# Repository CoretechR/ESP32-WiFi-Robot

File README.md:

# ESP32-WiFi-Robot
ESP32 Powered Video Streaming Robot

Python is needed to convert the website file from HTML to a single string and back.

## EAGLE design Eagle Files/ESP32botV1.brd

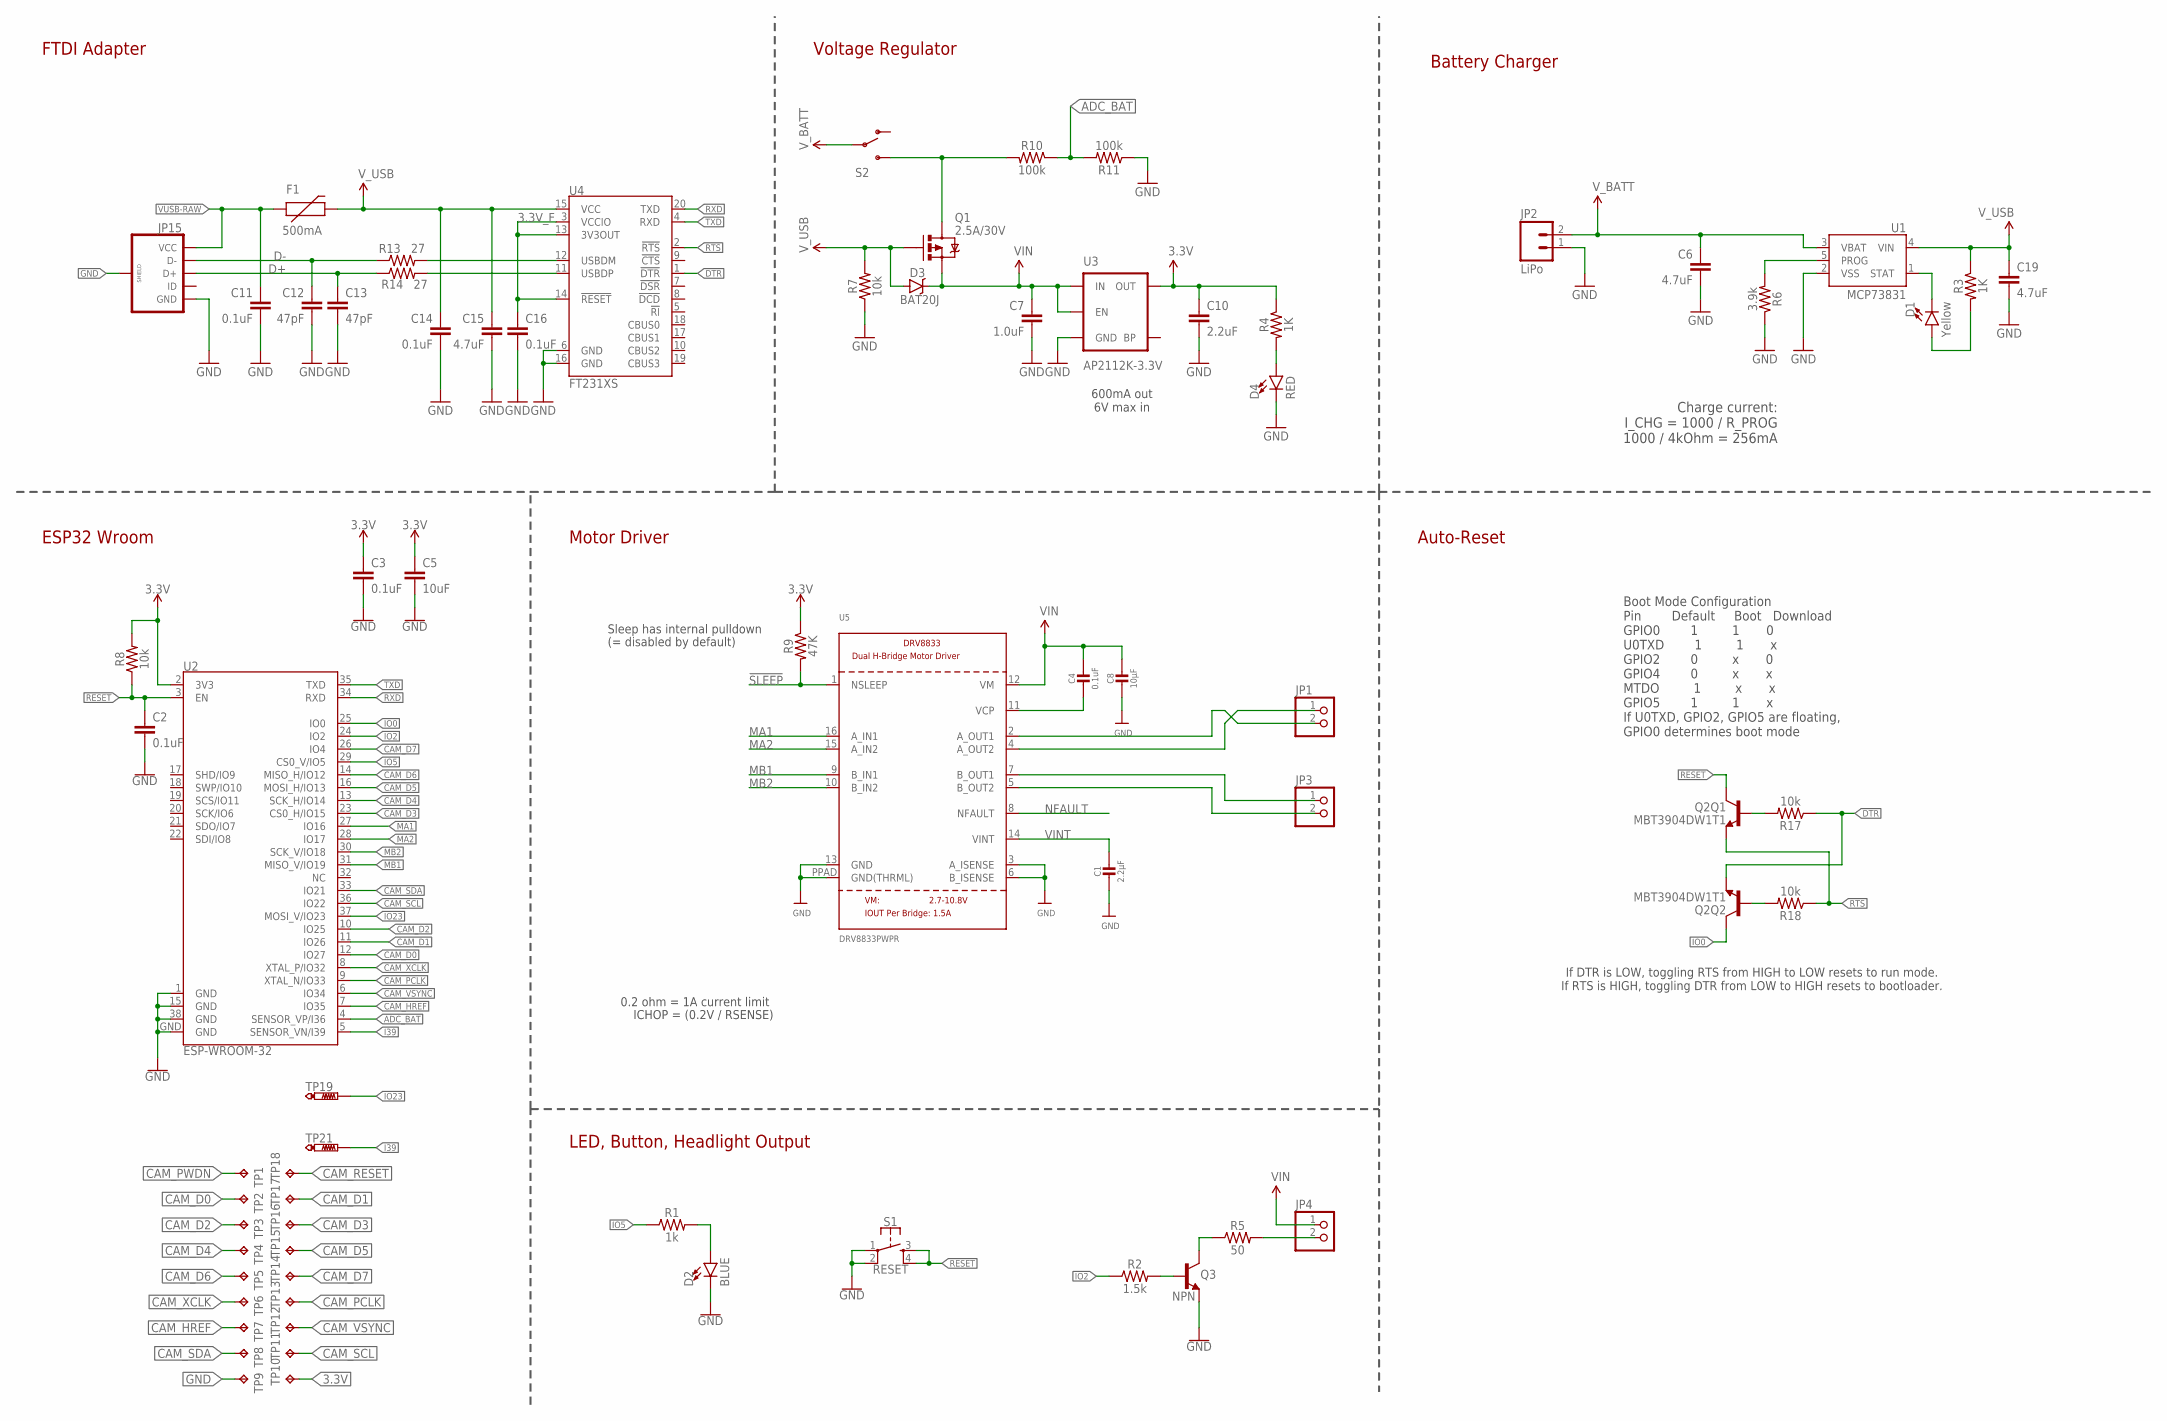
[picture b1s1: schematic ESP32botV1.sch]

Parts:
C1: 2.2µF; 0805-NO
C2, C3, C11, C14, C16: 0.1uF; 0603
C4: 0.1uF; 0805-NO
C5: 10uF; 0603
C6, C19: 4.7uF; 0603
C7: 1.0uF; 0805
C8: 10µF; 0805-NO
C10: 2.2uF; 0603
C12, C13: 47pF; 0603
C15: 4.7uF; 0603-CAP
D1: Yellow; LED-0603@1
D2: BLUE; LED-0603@2
D3: BAT20J; SOD-323
D4: RED; LED-0603
F1: 500mA; PTC-1206
JP1, JP3, JP4: HEADER-1X2ROUND; 1X02_ROUND
JP2: LiPo; JST-2-PTH
JP15: USB_MICROB_PLUGCONN-11752; USB-B-MICRO-SMD_V03
Q1: 2.5A/30V; SOT23-3
Q2: MBT3904DW1T1; SC70-6
Q3: NPN; SOT23-3
R1: 1k; 0603
R2: 1.5k; 0603
R3, R4: 1K; 0603
R5: 50; 0603
R6: 3.9k; 0603
R7, R8, R17, R18: 10k; 0603
R9: 47K; 0603
R10, R11: 100k; 0603
R13, R14: 27; 0603
S1: RESET; TACTILE_SWITCH_SMD_4.6X2.8MM
S2: SWITCH-SPDT-SMD-A; SWITCH-SPST-SMD-A
TP1, TP2, TP3, TP4, TP5, TP6, TP7, TP8, TP9, TP10, TP11, TP12, TP13, TP14, TP15, TP16, TP17, TP18: TPEC; EDGECONNECTOR
TP19, TP21: PTR1TP13R; TP13R
U1: MCP73831; SOT23-5
U2: ESP-WROOM-32
U3: AP2112K-3.3V; SOT23-5
U4: FT231XS; SSOP20_L
U5: DRV8833PWPR; HTSSOP16

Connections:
3.3V: C3.1, C5.1, C10.1, R4.1, R8.2, R9.1, TP10.TP, U2.2 (3V3), U3.5 (OUT)
3.3V_F: C16.1, U4.3 (VCCIO), U4.13 (3V3OUT), U4.14 (!RESET)
!SLEEP: R9.2, U5.1 (NSLEEP)
ADC_BAT: R10.1, R11.2, U2.4 (SENSOR_VP/I36)
AOUT1: JP1.2, U5.2 (A_OUT1)
AOUT2: JP1.1, U5.4 (A_OUT2)
BOUT1: JP3.1, U5.7 (B_OUT1)
BOUT2: JP3.2, U5.5 (B_OUT2)
CAM_D0: TP2.TP, U2.12 (IO27)
CAM_D1: TP17.TP, U2.11 (IO26)
CAM_D2: TP3.TP, U2.10 (IO25)
CAM_D3: TP16.TP, U2.23 (CS0_H/IO15)
CAM_D4: TP4.TP, U2.13 (SCK_H/IO14)
CAM_D5: TP15.TP, U2.16 (MOSI_H/IO13)
CAM_D6: TP5.TP, U2.14 (MISO_H/IO12)
CAM_D7: TP14.TP, U2.26 (IO4)
CAM_HREF: TP7.TP, U2.7 (IO35)
CAM_PCLK: TP13.TP, U2.9 (XTAL_N/IO33)
CAM_PWDN: TP1.TP
CAM_RESET: TP18.TP
CAM_SCL: TP11.TP, U2.36 (IO22)
CAM_SDA: TP8.TP, U2.33 (IO21)
CAM_VSYNC: TP12.TP, U2.6 (IO34)
CAM_XCLK: TP6.TP, U2.8 (XTAL_P/IO32)
D+: C13.1, JP15.D+, R14.1
D-: C12.1, JP15.D-, R13.1
DTR: Q2.1 (E), R17.1, U4.1 (!DTR)
GND: C1.2, C2.2, C3.2, C5.2, C6.2, C7.2, C8.2, C10.2, C11.2, C12.2, C13.2, C14.2, C15.2, C16.2, C19.2, D2.C, D4.C, JP2.1, JP15.GND, JP15.SHIELD1 (SHIELD), JP15.SHIELD2 (SHIELD), JP15.SHIELD3 (SHIELD), Q3.2 (E), R6.1, R7.1, R11.1, S1.1, S1.2, TP9.TP, U1.2 (VSS), U2.1 (GND), U2.15 (GND), U2.38 (GND), U2.GND, U3.2 (GND), U4.6 (GND), U4.16 (GND), U5.3 (A_ISENSE), U5.6 (B_ISENSE), U5.13 (GND), U5.PPAD (GND(THRML))
I39: TP21.TP, U2.5 (SENSOR_VN/I39)
IO0: Q2.6 (C), U2.25 (IO0)
IO2: R2.1, U2.24 (IO2)
IO5: R1.1, U2.29 (CS0_V/IO5)
IO23: TP19.TP, U2.37 (MOSI_V/IO23)
MA1: U2.27 (IO16), U5.16 (A_IN1)
MA2: U2.28 (IO17), U5.15 (A_IN2)
MB1: U2.31 (MISO_V/IO19), U5.9 (B_IN1)
MB2: U2.30 (SCK_V/IO18), U5.10 (B_IN2)
unnamed: D4.A, R4.2
unnamed: D2.A, R1.2
unnamed: JP4.2, R5.2
unnamed: Q1.3 (D), R10.2, S2.3 (S)
unnamed: R13.2, U4.12 (USBDM)
unnamed: R14.2, U4.11 (USBDP)
unnamed: D1.C, U1.1 (STAT)
unnamed: Q2.5 (B), R17.2
unnamed: Q2.2 (B), R18.2
unnamed: R6.2, U1.5 (PROG)
unnamed: D1.A, R3.2
unnamed: C4.2, U5.11 (VCP)
NFAULT: U5.8 (NFAULT)
OUT1: Q3.3 (C), R5.1
OUT1N: Q3.1 (B), R2.2
RESET: C2.1, Q2.3 (C), R8.1, S1.3, S1.4, U2.3 (EN)
RTS: Q2.4 (E), R18.1, U4.2 (!RTS)
RXD: U2.34 (RXD), U4.20 (TXD)
TXD: U2.35 (TXD), U4.4 (RXD)
VIN: C4.1, C7.1, C8.1, D3.C, JP4.1, Q1.2 (S), U3.1 (IN), U3.3 (EN), U5.12 (VM)
VINT: C1.1, U5.14 (VINT)
VUSB-RAW: C11.1, F1.1, JP15.VBUS (VCC)
V_BATT: C6.1, JP2.2, S2.2, U1.3 (VBAT)
V_USB: C14.1, C15.1, C19.1, D3.A, F1.2, Q1.1 (G), R3.1, R7.2, U1.4 (VIN), U4.15 (VCC)

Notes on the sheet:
Charge current: I_CHG = 1000 / R_PROG 1000 / 4kOhm = 256mA
Boot Mode Configuration Pin Default Boot Download GPIO0 1 1 0 U0TXD 1 1 x GPIO2 0 x 0 GPIO4 0 x x MTDO 1 x x GPIO5 1 1 x If U0TXD, GPIO2, GPIO5 are floating, GPIO0 determines boot mode
Auto-Reset
If DTR is LOW, toggling RTS from HIGH to LOW resets to run mode. If RTS is HIGH, toggling DTR from LOW to HIGH resets to bootloader.
LED, Button, Headlight Output
Voltage Regulator
600mA out 6V max in
0.2 ohm = 1A current limit
ICHOP = (0.2V / RSENSE)
Sleep has internal pulldown
(= disabled by default)
Battery Charger
FTDI Adapter
Motor Driver
ESP32 Wroom

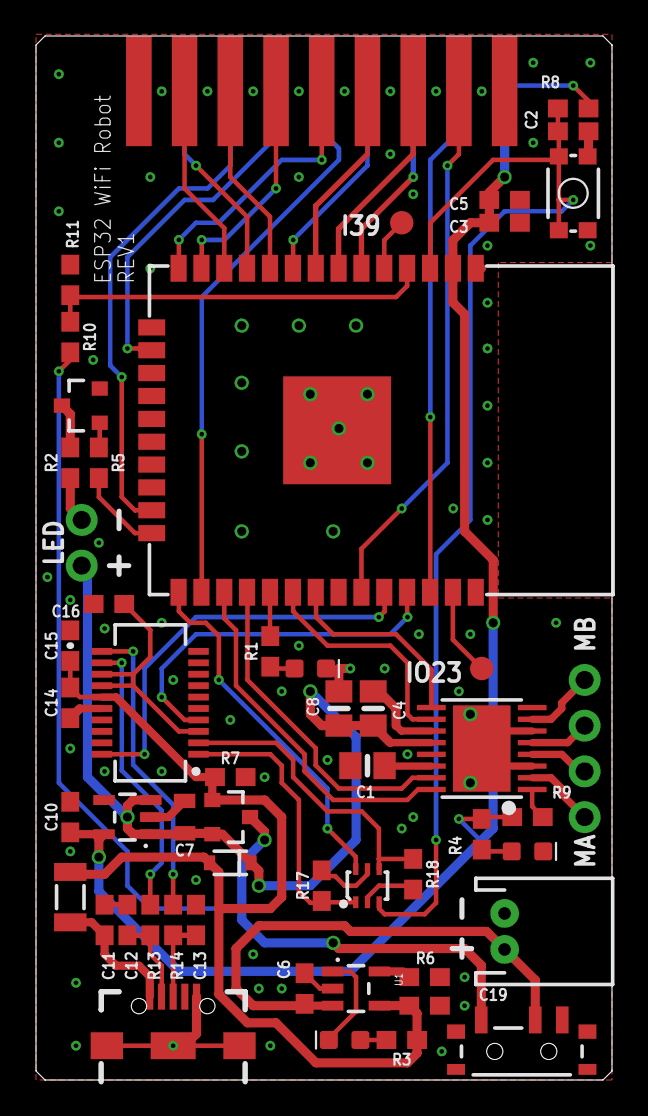
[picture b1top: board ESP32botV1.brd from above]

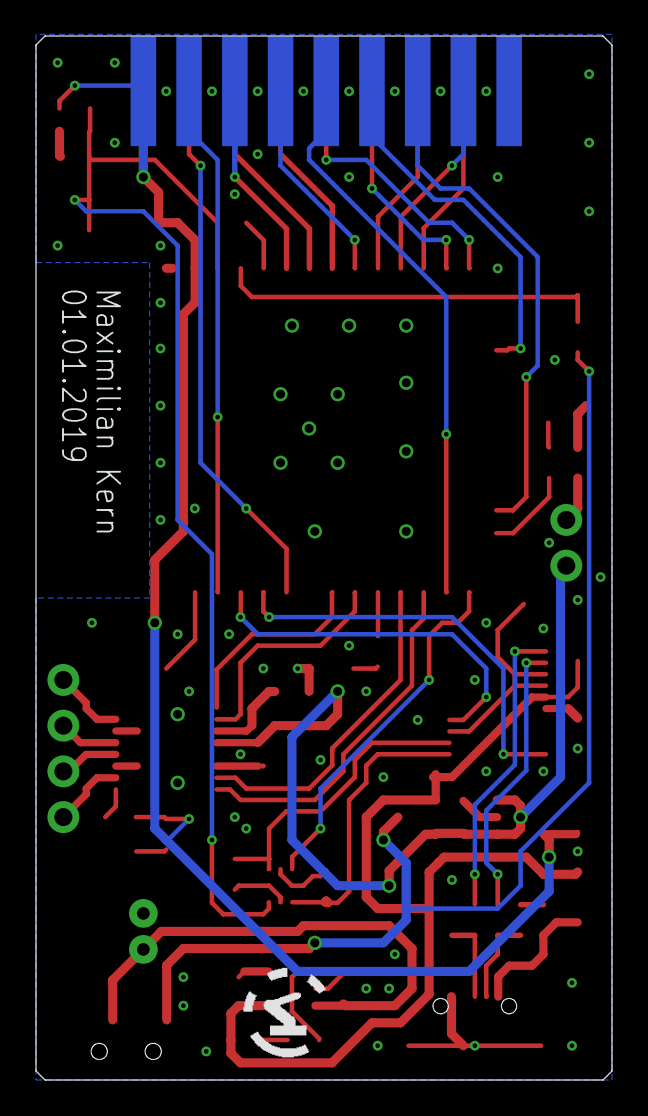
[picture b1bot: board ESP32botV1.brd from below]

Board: 2 copper layers, 32.0 x 58.0 mm, 71 parts (9 on the bottom side), 58 nets.

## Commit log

2019-01-22 Initial Upload
2019-01-22 Eagle files added
2019-01-27 Schematic PDF added
2019-01-29 Added shutdown command
2019-02-07 Added Image Capture Feature
    The middle button does now save the current image of the stream in 120*160px

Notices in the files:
parts and their libraries:
SparkFun-RF: Licensing: Creative Commons ShareAlike 4.0 International - https://creativecommons.org/licenses/by-sa/4.0
SparkFun-DigitalIC: Licensing: CC v3.0 Share-Alike You are welcome to use this library for commercial purposes.
